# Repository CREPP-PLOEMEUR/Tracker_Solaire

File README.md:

<!--# Tracker solaire -->
<!--+ 2023-2024 -->
<!--$ C++-->
<!--$ Freecad -->
<!--$ GPS -->
<!--% Ce projet vise à concevoir et construire un système de suivi solaire spécialement conçu pour maximiser l'efficacité de la capture d'énergie solaire à partir d'un panneau solaire. -->
 -->
# Projet de Tracker Solaire pour Panneau 1m x 1m60

Ce projet vise à concevoir et construire un système de suivi solaire spécialement conçu pour maximiser l'efficacité de la capture d'énergie solaire à partir d'un panneau solaire de dimensions spécifiques.

## Table des matières

- [Aperçu](#aperçu)
- [Fonctionnalités](#fonctionnalités)
- [Matériaux](#matériaux)
- [Schémas et Conception](#schémas-et-conception)

## Aperçu

Ce projet a pour objectif de créer un tracker solaire qui ajuste automatiquement la position d'un panneau solaire de 1 mètre sur 1 mètre 60 pour suivre le mouvement du soleil tout au long de la journée. Cette optimisation permettra une captation maximale de l'énergie solaire disponible.

## Fonctionnalités

Le tracker solaire comprend différentes fonctionnalités :

- Suivi précis et automatique de la trajectoire du soleil pour maximiser la production d'énergie solaire.
- Utilisation d'un module GPS pour déterminer la position du panneau solaire.  Une fois la position captée, l'heure permet de calculer 
la position du Soleil à n'importe quel moment de la journée.
- Un module RTC (Real Time Clock) enregistre l'heure pour éviter de solliciter le module GPS
- Contrôle fluide des moteurs pour ajuster la position du panneau solaire 
- Interface de communication pour surveiller et configurer les performances du tracker.
- Tous les évènements sont enregistrés dans une carte microSD.
- Le tracker se met en veille profonde dès que la luminosité devient trop faible.
- Une rafale de vent, dont la consigne peut être ajustée par l'utilisateur, réveille en cas de besoin le tracker pour le mettre en position horizontale.

## Matériaux

- Composants électroniques standard tels que microcontrôleurs, GPS, moteurs pas à pas, etc.
- Carte de circuit imprimé spécialement conçue pour le tracker solaire.

- Moteurs pas à pas robustes adaptés aux dimensions du panneau solaire.
- Structure mécanique pour soutenir et orienter le panneau solaire.
- Source d'alimentation adaptée aux moteurs et à l'électronique.

## Schémas et Conception

Les schémas électriques détaillés et les plans de conception du circuit imprimé spécifique au tracker solaire sont disponibles dans le dossier `Hardware`.

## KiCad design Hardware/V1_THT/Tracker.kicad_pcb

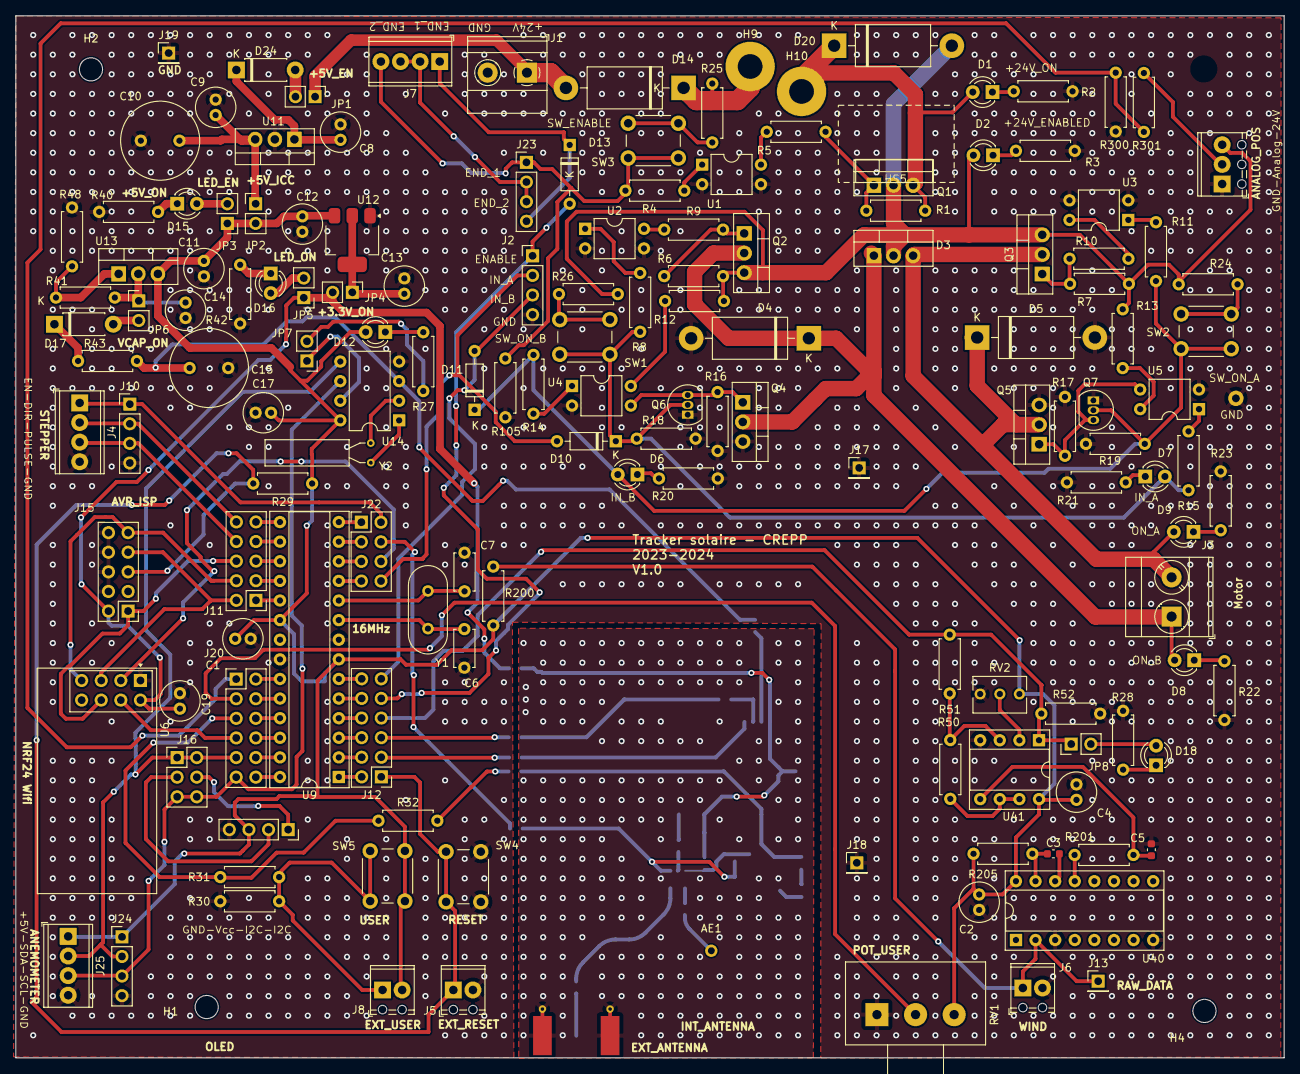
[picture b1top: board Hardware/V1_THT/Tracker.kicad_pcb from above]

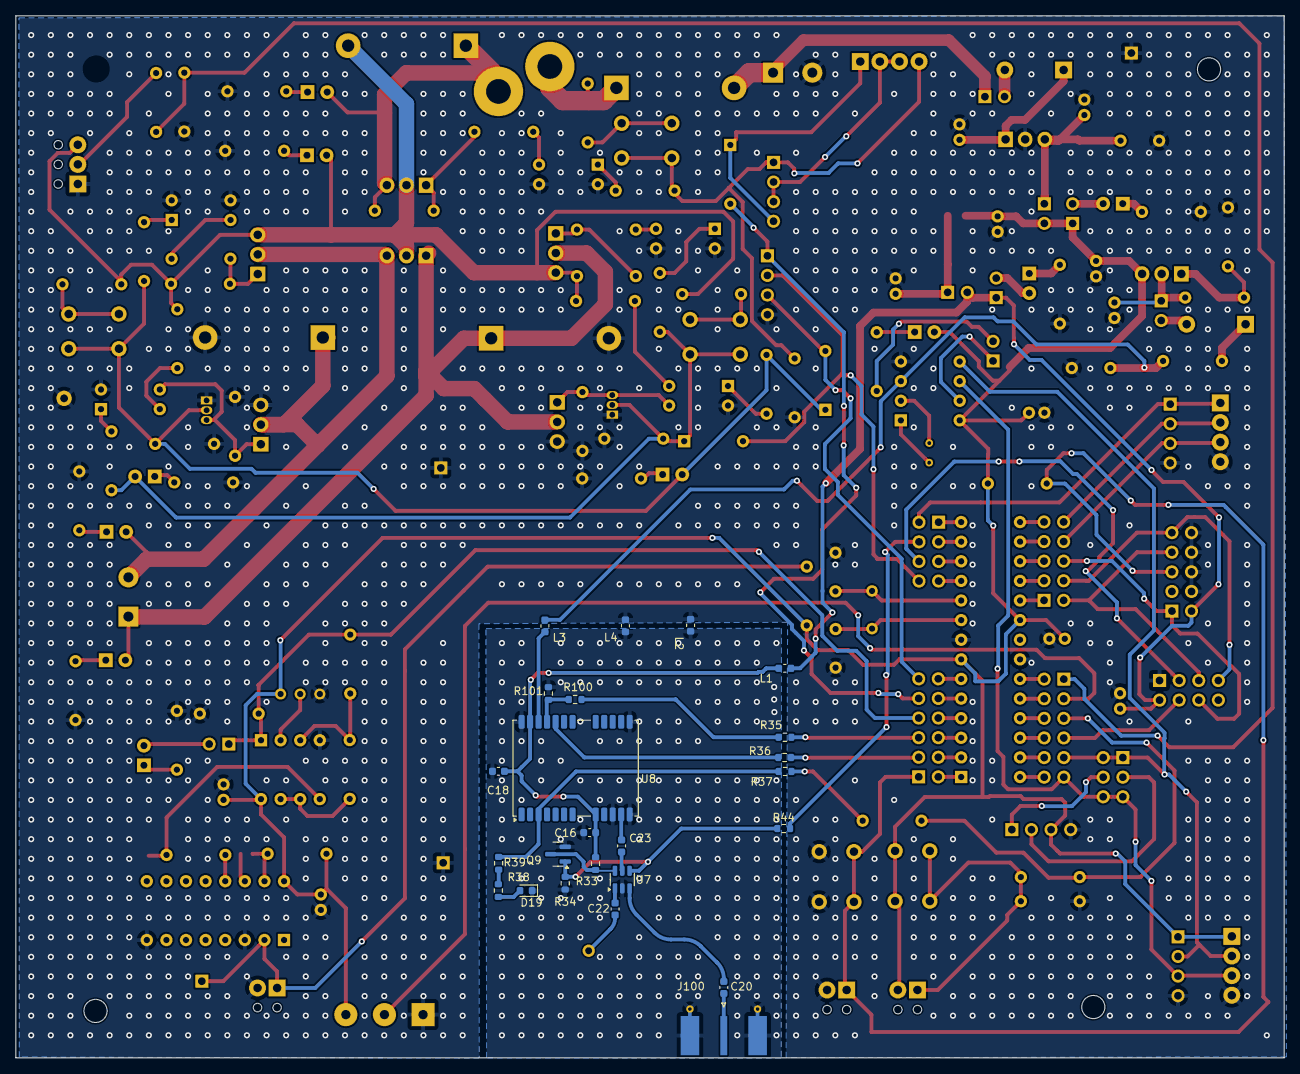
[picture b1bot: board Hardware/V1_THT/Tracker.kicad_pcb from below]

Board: 2 copper layers, 164.3 x 134.9 mm, 181 parts (24 on the bottom side), 132 nets.

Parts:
AE1: Internal_antenna; MountingHole_2.2mm_M2_DIN965_Pad
C1, C2, C4, C8, C9, C11, C12, C13, C14, C17, C19: 100nF; C_Radial_D5.0mm_H11.0mm_P2.00mm
C3, C5, C16, C18: 100nF; C_0603_1608Metric
C6, C7: 22pF; C_Disc_D4.7mm_W2.5mm_P5.00mm
C10: 1mF; C_Radial_D10.0mm_H16.0mm_P5.00mm
C15: 20F; C_Radial_D10.0mm_H20.0mm_P5.00mm
C20, C22, C23: 100pF; C_0603_1608Metric
D1, D2, D6, D7, D8, D9, D12, D15, D16, D18: LED; LED_D3.0mm
D3: D_Dual_CommonCathode_AAK; TO-220-3_Vertical
D4, D5, D14, D20: 1N5408; D_DO-201AD_P15.24mm_Horizontal
D10, D11, D13: 1N4148; D_DO-35_SOD27_P7.62mm_Horizontal
D17, D24: 1N4818; D_DO-41_SOD81_P7.62mm_Horizontal
D19: LED; LED_0603_1608Metric
H1, H2, H3, H4: MountingHole; MountingHole_3mm
H8: Probe_GND; Hole_1mm_Scope
H9, H10: MountingHole_Pad; MountingHole_3.2mm_M3_Pad
HS1, HS2, HS3, HS4, HS5: Heatsink; HeastSink_MOSFET_15mm_10mm_20mm
J1: +24V; TerminalBlock_Phoenix_MKDS-1,5-2-5.08_1x02_P5.08mm_Horizont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
J2, J10, J24: PinHeader_Control; PinHeader_1x04_P2.54mm_Vertical
J3: Motor; TerminalBlock_Phoenix_MKDS-3-2-5.08_1x02_P5.08mm_Horizontal
J4: Stepper; TerminalBlock_Phoenix_MPT-0,5-4-2.54_1x04_P2.54mm_Horizontal
J5, J8: USR_BTN; TerminalBlock_Phoenix_MPT-0,5-2-2.54_1x02_P2.54mm_Horizontal
J6: Wind; TerminalBlock_Phoenix_MPT-0,5-2-2.54_1x02_P2.54mm_Horizontal
J7: END_STOP_1_2; TerminalBlock_Phoenix_MPT-0,5-4-2.54_1x04_P2.54mm_Horizontal
J9: Analog_Position; TerminalBlock_Phoenix_MPT-0,5-3-2.54_1x03_P2.54mm_Horizontal
J11: Conn_02x05_Odd_Even; PinHeader_2x05_P2.54mm_Vertical
J12, J20: Conn_02x06_Odd_Even; PinHeader_2x06_P2.54mm_Vertical
J13: RAW_data_Wind; PinHeader_1x01_P2.54mm_Vertical
J14: OLED_SOCKET; PinSocket_1x04_P2.54mm_Vertical
J15: SPI_Programming; PinHeader_2x05_P2.54mm_Vertical
J16: I2C_Selector; PinHeader_2x03_P2.54mm_Vertical
J17, J18, J19: GND; PinHeader_1x01_P2.54mm_Vertical
J22: Conn_02x04_Odd_Even; PinHeader_2x04_P2.54mm_Vertical
J23: END_STOP_header; PinHeader_1x04_P2.54mm_Vertical
J25: Anemometer; TerminalBlock_Phoenix_MPT-0,5-4-2.54_1x04_P2.54mm_Horizontal
J100: 132134; SMA_Molex_73251-1153_EdgeMount_Horizontal
JP1, JP2, JP3, JP4, JP5, JP6, JP7, JP8: Jumper; PinHeader_1x02_P2.54mm_Vertical
L1, L2, L3, L4: L; L_0603_1608Metric
Q1, Q2, Q3: IRF4905; TO-220-3_Vertical
Q4, Q5: IRF520; TO-220-3_Vertical
Q6, Q7: 2N7000; TO-92_Inline
Q9: SI2302; SOT-23
R1, R25, R30, R31: 1k; R_Axial_DIN0207_L6.3mm_D2.5mm_P7.62mm_Horizontal
R2, R3, R22, R23: 3.3K; R_Axial_DIN0207_L6.3mm_D2.5mm_P7.62mm_Horizontal
R4, R8, R11, R14, R15: 120; R_Axial_DIN0207_L6.3mm_D2.5mm_P7.62mm_Horizontal
R5, R9, R10: 2.2K; R_Axial_DIN0207_L6.3mm_D2.5mm_P7.62mm_Horizontal
R6, R7, R12, R13: 1K; R_Axial_DIN0207_L6.3mm_D2.5mm_P7.62mm_Horizontal
R16, R17, R18, R19: 100k; R_Axial_DIN0207_L6.3mm_D2.5mm_P7.62mm_Horizontal
R20, R21, R27, R28, R40, R42: 270; R_Axial_DIN0207_L6.3mm_D2.5mm_P7.62mm_Horizontal
R24, R26: 2.7k; R_Axial_DIN0207_L6.3mm_D2.5mm_P7.62mm_Horizontal
R29, R50, R51, R52, R105, R201, R205, R300, R301: 10k; R_Axial_DIN0207_L6.3mm_D2.5mm_P7.62mm_Horizontal
R32: 2.2k; R_Axial_DIN0207_L6.3mm_D2.5mm_P7.62mm_Horizontal
R33, R100, R101: 1k; R_0603_1608Metric
R34: 10k; R_0603_1608Metric
R35, R36, R37, R39, R44: 0; R_0603_1608Metric
R38: 330; R_0603_1608Metric
R41, R43, R48: 100; R_Axial_DIN0207_L6.3mm_D2.5mm_P7.62mm_Horizontal
R200: 470k; R_Axial_DIN0207_L6.3mm_D2.5mm_P7.62mm_Horizontal
RV1: R_Potentiometer; Potentiometer_Alps_RK163_Single_Horizontal
RV2: R_Potentiometer; Potentiometer_Bourns_3266Y_Vertical
SW1: SW_A; SW_PUSH_6mm_H8mm
SW2, SW4: SW_B; SW_PUSH_6mm_H8mm
SW3: SW_E; SW_PUSH_6mm_H8mm
SW5: SW_User; SW_PUSH_6mm_H8mm
U1, U2, U3, U4, U5: PC817; DIP-4_W7.62mm
U6: NRF24L01_Breakout; nRF24L01_Breakout
U7: AS193-73; SOT-23-6
U8: NEO-M8M; ublox_NEO
U9: ATmega328P-P; DIP-28_W7.62mm_Socket
U11: L7805; TO-220-3_Vertical
U12: AMS1117-3.3; SOT-223-3_TabPin2
U13: LM317_TO-220; TO-220-3_Vertical
U14: DS1307+; DIP-8_W7.62mm
U40: 74HC123; DIP-16_W7.62mm_Socket
U41: LM358; DIP-8_W7.62mm_Socket
Y1: 16MHz; Crystal_HC49-4H_Vertical
Y2: 16MHz; Crystal_AT310_D3.0mm_L10.0mm_Horizontal

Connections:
+3.3V: C19.1, J15.2, JP4.2 (B), JP5.1 (A), L1.1, U6.2 (VCC)
+3.3V_GNSS: C16.2, C18.2, L1.2, R33.2, U8.8 (~RESET), U8.23 (VCC)
+5V: C1.2, C2.1, C4.1, C11.1, C12.1, C17.2, D12.2 (A), J8.2, J14.3, J24.1, J25.1, JP2.2 (B), JP3.1 (A), R29.1, R200.1, R205.1, RV1.3, RV2.1, SW5.1 (A), U9.7 (VCC), U9.20 (AVCC), U12.3 (VI), U13.3 (VI), U14.8 (VCC), U40.16 (VCC), U41.8 (V+)
+24V: D14.2 (A), J1.1, JP1.1 (A)
+VCC_Motor: D2.2 (A), D3.2 (K), D20.2 (A), J9.3, Q1.2 (D), Q2.3 (S), Q3.3 (S), R6.1, R7.1, R12.1, R13.1, R24.1, R26.1
+VCap: C15.1, L3.1, R43.2, U14.3 (VBAT)
+VCap_GNSS: L3.2, U8.22 (V_BCKP)
/Anemometer/SCL: J16.5, J16.6, J20.11, J24.3, J25.3, U14.6 (SCL)
/Anemometer/SDA: J16.1, J16.2, J20.9, J24.2, J25.2, U14.5 (SDA)
/Crystal/XTAl_1: C6.2, U9.9 (XTAL1/PB6), Y1.2
/Crystal/XTAl_2: C7.2, U9.10 (XTAL2/PB7), Y1.1
/GNSS/RX: J12.3, R36.1
/GNSS/TX: J12.5, R35.1
/GNSS/~INTERNAL_ANTENNA: Q9.1 (G), R34.2, R44.1, U7.4 (V2)
/MCU/CLK: J11.2, J15.7, U6.5 (SCK)
/MCU/MISO: J11.4, J15.9, U6.7 (MISO)
/MCU/MOSI: J11.6, J15.1, U6.6 (MOSI)
/MCU/PB0: J22.1, U9.14 (PB0)
/MCU/PB0-D8: J4.1, J10.1, J22.2
/MCU/PB1-D9~: J4.2, J10.2, J11.10
/MCU/PB2-D10~: J4.3, J10.3, J11.8
/MCU/PC0-A0: J20.1, R300.2, R301.2
/MCU/PC1-A1: J20.3, RV1.2
/MCU/PC3-A3: J20.7, U6.4 (~CSN)
/MCU/PD2-D2-(INT0): J12.7, JP8.1 (A), R51.2, R52.2, U41.1
/MCU/PD3-D3-(INT1)~: D13.2 (A), J2.1, J12.9
/MCU/PD4-D4: D11.2 (A), J2.3, J12.11
/MCU/PD5-D5~: D10.2 (A), J2.2, J22.8
/MCU/PD6-D6~: J22.6, U6.3 (CE)
/MCU/PD7-D7: J22.4, R44.2
/Motors/ENABLE: D13.1 (K), J7.1, J23.4
/Motors/IN_A: D7.2 (A), D10.1 (K), Q6.2 (G), R8.1, R15.2, R18.1, SW1.1 (A)
/Motors/IN_B: D6.2 (A), D11.1 (K), Q7.2 (G), R11.2, R14.1, R19.1, SW2.1 (A)
/OLED/A: J14.1, J16.4
/OLED/B: J14.2, J16.3
/Power_Supply/Vcapa: C14.1, JP6.1 (A), R41.2, U13.2 (VO)
/RST: J5.1, J12.1, J15.5, R29.2, SW4.2 (B)
/TIMEPULSE: R32.2, R37.2
/UserActions/Button: J8.1, R30.1, R31.2, SW5.2 (B)
/V_{A_{2}}: J20.5, R31.1, R32.1
GND: C1.1, C2.2, C4.2, C5.2, C6.1, C7.1, C8.2, C9.2, C10.2, C11.2, C12.2, C13.2, C14.2, C15.2, C17.1, C19.2, D4.2 (A), D5.2 (A), H8.1, J1.2, J2.4, J4.4, J5.2, J6.2, J9.1, J10.4, J14.4, J15.4, J15.6, J15.8, J15.10, J17.1, J18.1, J19.1, J24.4, J25.4, L2.1, L4.1, Q4.3 (S), Q5.3 (S), Q6.1 (S), Q7.1 (S), R2.2, R3.2, R16.2, R17.2, R18.2, R19.2, R20.2, R21.2, R22.2, R23.2, R28.2, R30.2, R40.2, R42.2, R48.1, R52.1, R105.2, R300.1, RV1.1, RV2.3, SW4.1 (A), U1.2, U1.3, U2.2, U2.3, U3.2, U3.3, U4.2, U5.2, U6.1 (GND), U9.8 (GND), U9.22 (GND), U11.2 (GND), U12.1 (GND), U14.4 (GND), U40.3 (Clr), U40.8 (GND), U41.4 (V-)
GND_GNSS: C16.1, C18.1, D19.1 (K), J100.2 (Ext), L2.2, L4.2, Q9.2 (S), R34.1, R101.2, U7.2 (GND), U8.10 (GND), U8.12 (GND), U8.13 (GND), U8.24 (GND)
unnamed: AE1.1 (A), C22.1
unnamed: D1.2 (A), D20.1 (K), H10.1, Q1.3 (S), R1.2
unnamed: D1.1 (K), R2.1
unnamed: D2.1 (K), R3.1
unnamed: D3.1 (A), D4.1 (K), D8.2 (A), J3.1, Q2.2 (D), Q4.2 (D)
unnamed: D3.3 (A), D5.1 (K), D9.2 (A), J3.2, Q3.2 (D), Q5.2 (D)
unnamed: D6.1 (K), R20.1
unnamed: D7.1 (K), R21.1
unnamed: D8.1 (K), R22.1
unnamed: D9.1 (K), R23.1
unnamed: D12.1 (K), R27.1
unnamed: D14.1 (K), H9.1, R25.1
unnamed: D15.2 (A), JP3.2 (B)
unnamed: D15.1 (K), R40.1
unnamed: D16.2 (A), JP5.2 (B)
unnamed: D16.1 (K), R42.1
unnamed: D17.2 (A), JP6.2 (B)
unnamed: D17.1 (K), R43.1
unnamed: D18.2 (A), JP8.2 (B)
unnamed: D18.1 (K), R28.1
unnamed: D19.2 (A), R38.1
unnamed: D24.2 (A), JP1.2 (B)
unnamed: C8.1, D24.1 (K), U11.1 (IN)
unnamed: J9.2, R301.1
unnamed: J11.1, U9.19 (PB5)
unnamed: J11.3, U9.18 (PB4)
unnamed: J11.5, U9.17 (PB3)
unnamed: J11.7, U9.16 (PB2)
unnamed: J11.9, U9.15 (PB1)
unnamed: J12.2, U9.1 (~RESET/PC6)
unnamed: J12.4, U9.2 (PD0)
unnamed: J12.6, U9.3 (PD1)
unnamed: J12.8, U9.4 (PD2)
unnamed: J12.10, U9.5 (PD3)
unnamed: J12.12, U9.6 (PD4)
unnamed: J6.1, J13.1, R200.2, U40.2 (B)
unnamed: J20.2, U9.23 (PC0)
unnamed: J20.4, U9.24 (PC1)
unnamed: J20.6, U9.25 (PC2)
unnamed: J20.8, U9.26 (PC3)
unnamed: J20.10, U9.27 (PC4)
unnamed: J20.12, U9.28 (PC5)
unnamed: J22.3, U9.13 (PD7)
unnamed: J22.5, U9.12 (PD6)
unnamed: J22.7, U9.11 (PD5)
unnamed: J7.4, J23.1, R4.1, R105.1, SW3.1 (A)
unnamed: J7.2, J7.3, J23.2, J23.3
unnamed: C20.1, J100.1 (In)
unnamed: C9.1, C10.1, JP2.1 (A), U11.3 (OUT)
unnamed: C13.1, JP4.1 (A), U12.2 (VO)
unnamed: JP7.1 (A), U14.7 (SQW/OUT)
unnamed: JP7.2 (B), R27.2
unnamed: Q1.1 (G), R1.1, R5.2
unnamed: Q2.1 (G), R6.2, R9.2
unnamed: Q3.1 (G), R7.2, R10.2
unnamed: Q4.1 (G), Q6.3 (D), R16.1, U4.3
unnamed: Q5.1 (G), Q7.3 (D), R17.1, U5.3
unnamed: Q9.3 (D), R33.1, U7.6 (V1)
unnamed: R4.2, U1.1
unnamed: R5.1, U1.4
unnamed: R8.2, U2.1
unnamed: R9.1, U2.4
unnamed: R10.1, U3.4
unnamed: R11.1, U3.1
unnamed: R12.2, U4.4
unnamed: R13.2, U5.4
unnamed: R14.2, U4.1
unnamed: R15.1, U5.1
unnamed: R38.2, R39.1
unnamed: R35.2, R100.1
unnamed: R26.2, SW1.2 (B)
unnamed: R24.2, SW2.2 (B)
unnamed: R25.2, SW3.2 (B)
unnamed: C22.2, U7.1 (RF1)
unnamed: C20.2, U7.3 (RF2)
unnamed: C23.1, U7.5 (RFC)
unnamed: C23.2, U8.11 (RF_IN)
unnamed: R100.2, R101.1, U8.21 (RXD/SPI_MOSI)
unnamed: R37.1, R39.2, U8.3 (TIMEPULSE)
unnamed: R36.2, U8.20 (TXD/SPI_MISO)
unnamed: R41.1, R48.2, U13.1 (ADJ)
unnamed: U14.1 (X1), Y2.2
unnamed: U14.2 (X2), Y2.1
unnamed: C3.2, U40.14 (Cext)
unnamed: R201.1, U40.13 (Q)
unnamed: C3.1, R205.2, U40.15 (RCext)
unnamed: R50.2, R51.1, U41.3 (+)
unnamed: RV2.2, U41.2 (-)
unnamed: C5.1, R201.2, U41.5 (+)
unnamed: R50.1, U41.6 (-), U41.7

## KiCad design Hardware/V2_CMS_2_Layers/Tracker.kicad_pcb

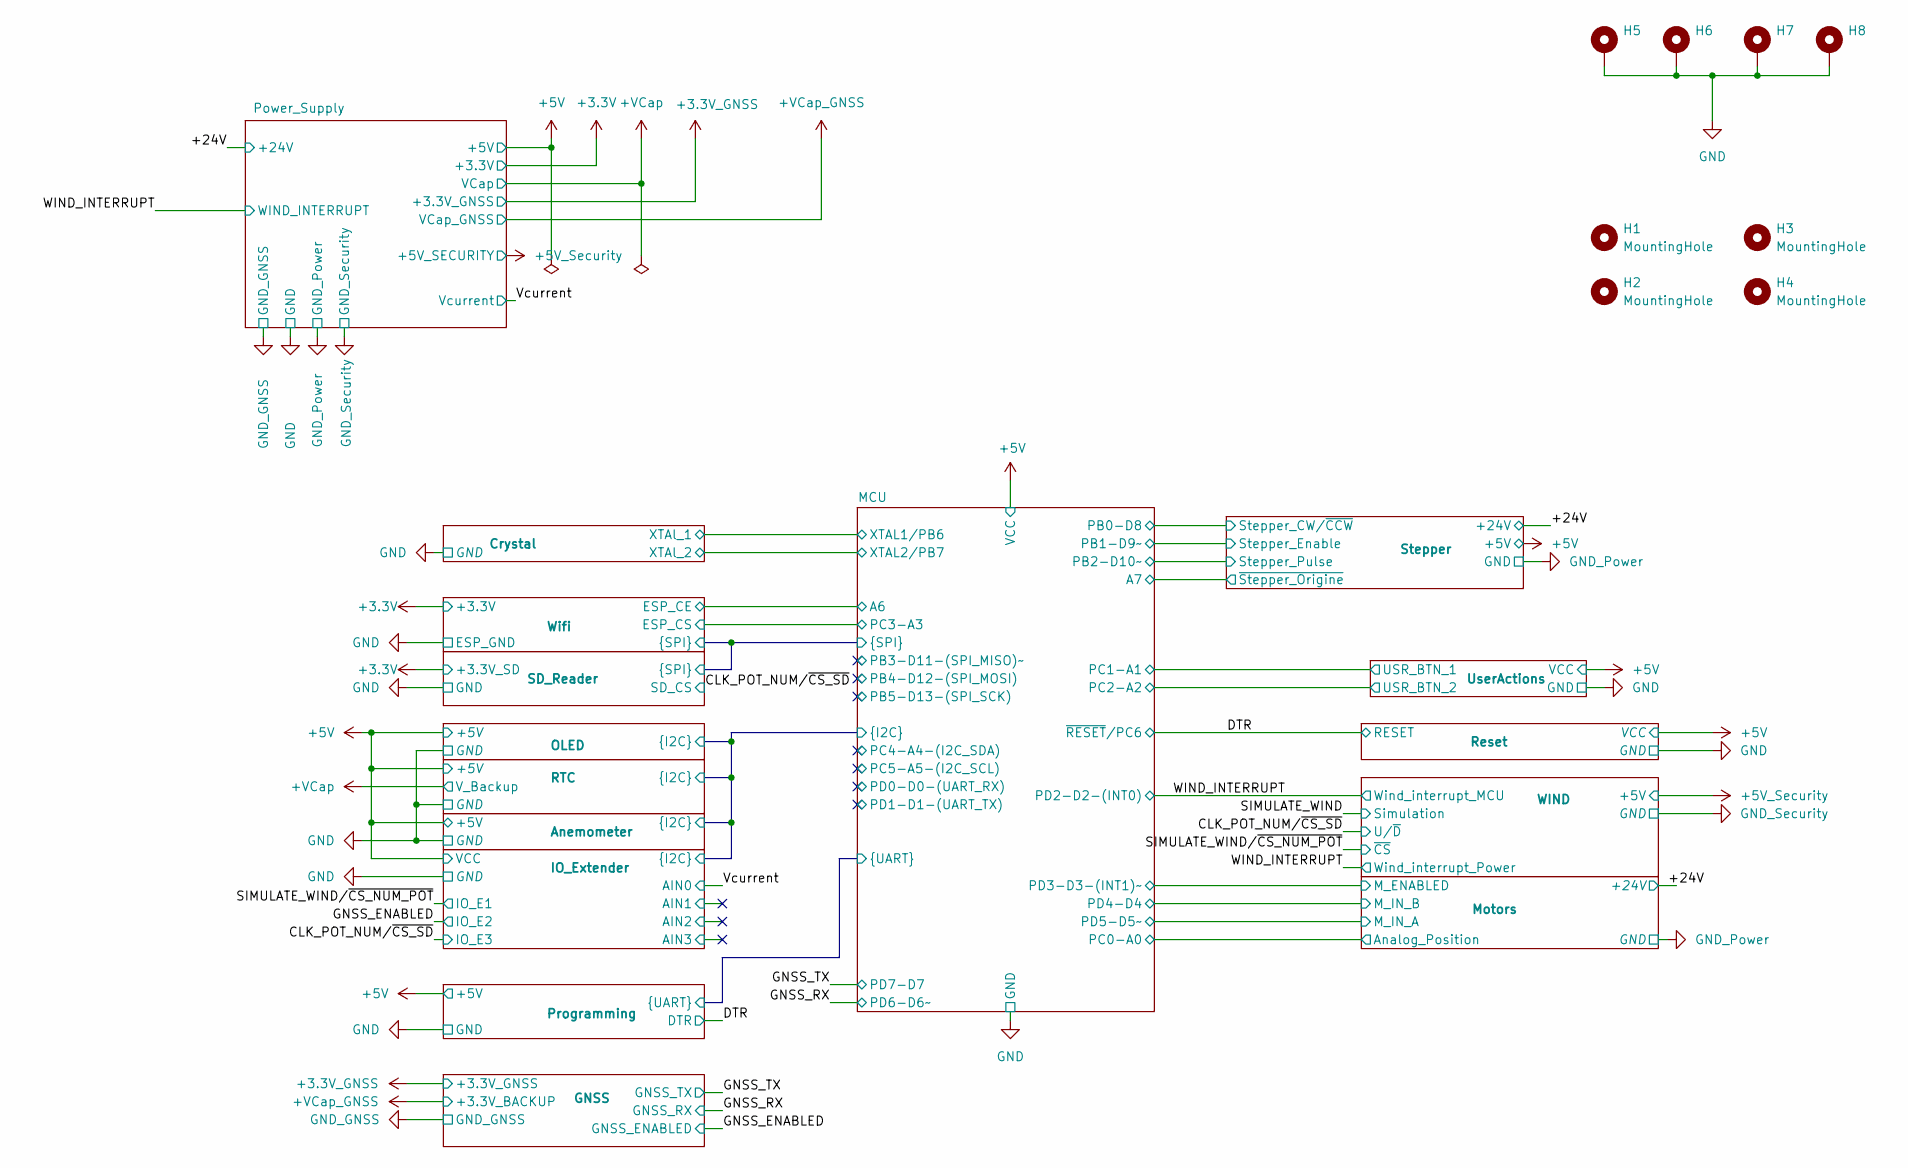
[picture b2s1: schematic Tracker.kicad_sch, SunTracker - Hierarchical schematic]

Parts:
H1, H2, H3, H4: MountingHole; MountingHole_3mm
H5, H6, H7, H8: Probe_GND; Hole_1mm_Scope

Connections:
unnamed: H5.1, H6.1, H7.1, H8.1

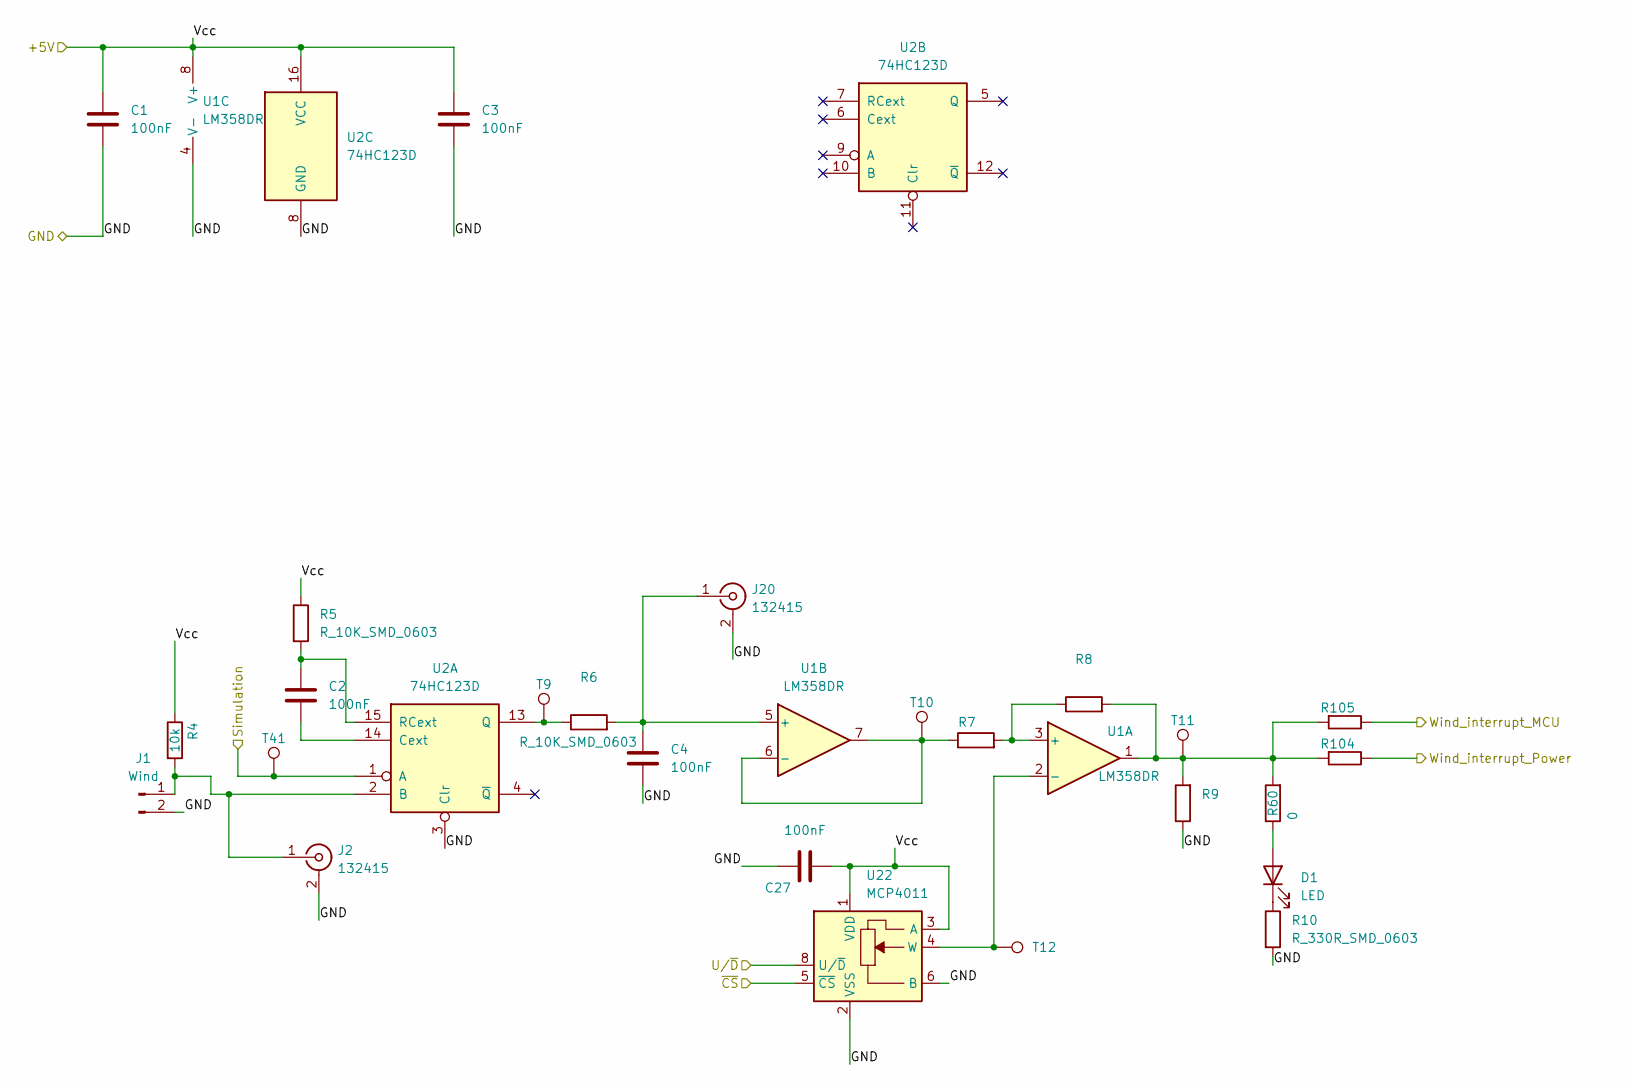
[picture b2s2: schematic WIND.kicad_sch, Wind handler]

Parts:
C1, C2, C3, C4, C27: 100nF; C_0603_1608Metric
D1: LED; LED_0603_1608Metric
J1: Wind; TerminalBlock_Phoenix_MPT-0,5-2-2.54_1x02_P2.54mm_Horizontal
J2, J20: 132415; SMA_Molex_73251-1153_EdgeMount_Horizontal
R4: 10k; R_0603_1608Metric
R5, R6, R7, R8, R9: R_10K_SMD_0603; R_0603_1608Metric
R10: R_330R_SMD_0603; R_0603_1608Metric
R60: 0; R_0603_1608Metric
R104, R105: R_0R_SMD_0603; R_0603_1608Metric
T9, T10, T11, T12, T41: TP; TestPoint_Pad_D1.0mm
U1: LM358DR; TSSOP-8_4.4x3mm_P0.65mm
U2: 74HC123D; SOIC-16W_5.3x10.2mm_P1.27mm
U22: MCP4011; SOIC-8_3.9x4.9mm_P1.27mm

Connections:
/CLK_POT_NUM/~CS_SD: U22.8 (U/~D); also elsewhere on the board
/SIMULATE_WIND: T41.1, U2.1 (A)
/SIMULATE_WIND/~CS_NUM_POT: U22.5 (~CS); also elsewhere on the board
/WIND_INTERRUPT: R104.2, R105.2; also elsewhere on the board
unnamed: D1.2 (A), R60.1
unnamed: D1.1 (K), R10.1
unnamed: J1.1, J2.1 (In), R4.2, U2.2 (B)
unnamed: C4.1, J20.1 (In), R6.2, U1.5 (+)
unnamed: R8.2, R9.2, R60.2, R104.1, R105.1, T11.1, U1.1
unnamed: R7.2, R8.1, U1.3 (+)
unnamed: T12.1, U1.2 (-), U22.4 (W)
unnamed: R7.1, T10.1, U1.6 (-), U1.7
unnamed: C2.2, U2.14 (Cext)
unnamed: R6.1, T9.1, U2.13 (Q)
unnamed: C2.1, R5.2, U2.15 (RCext)

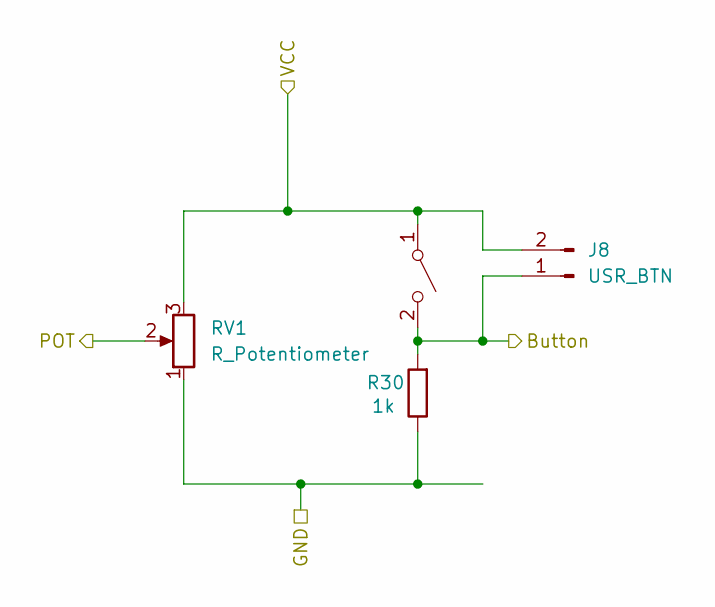
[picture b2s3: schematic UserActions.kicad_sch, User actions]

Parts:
J8: USR_BTN; TerminalBlock_Phoenix_MPT-0,5-2-2.54_1x02_P2.54mm_Horizontal
R30: 1k; R_Axial_DIN0207_L6.3mm_D2.5mm_P7.62mm_Horizontal
RV1: R_Potentiometer; Potentiometer_Alps_RK163_Single_Horizontal
SW5: SW_User; SW_PUSH_6mm_H8mm

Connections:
unnamed 225: RV1.2; also elsewhere on the board

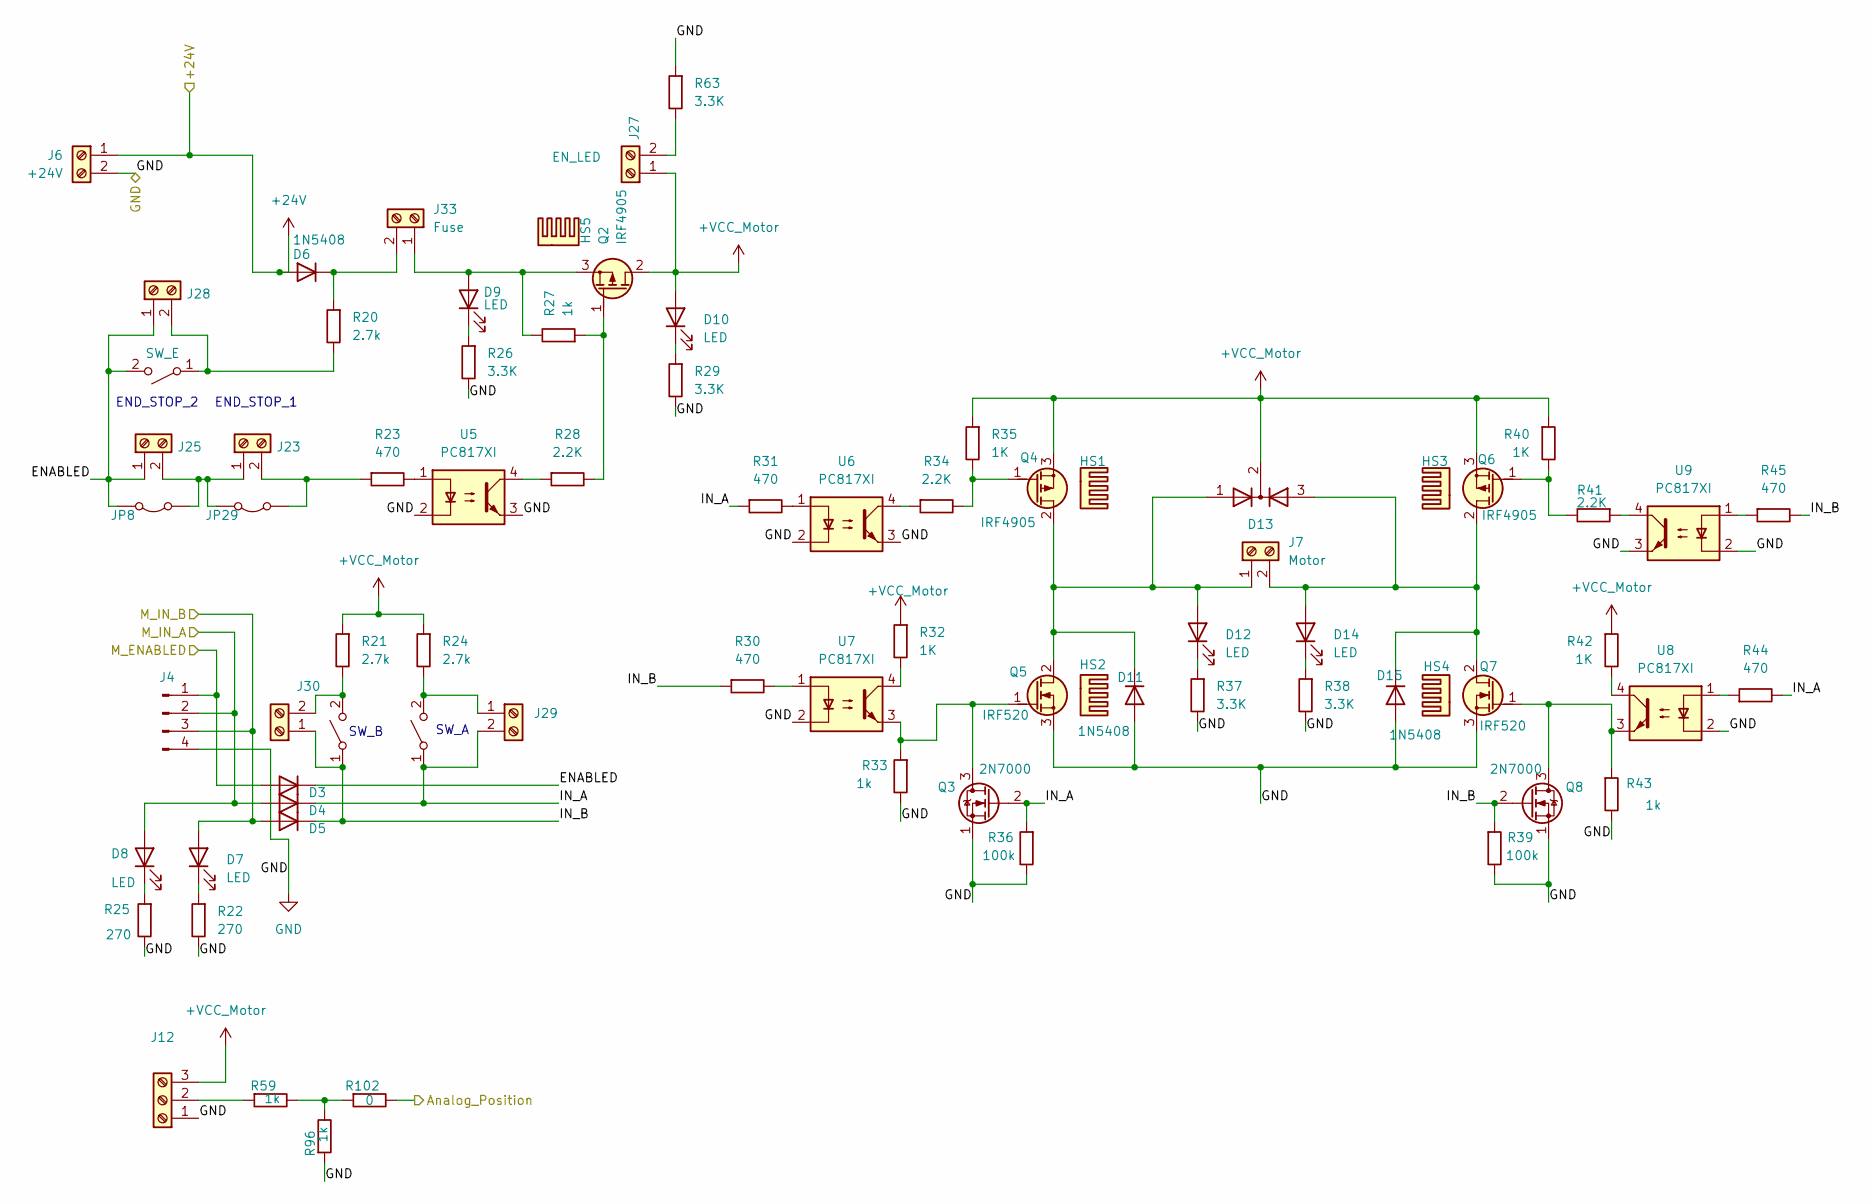
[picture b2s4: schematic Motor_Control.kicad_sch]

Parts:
D3, D4, D5: 1N4148; D_SOD-323
D6, D11, D15: 1N5408; D_DO-201AD_P15.24mm_Horizontal
D7, D8, D9, D10, D12, D14: LED; LED_0603_1608Metric
D13: D_Dual_CommonCathode_AAK; TO-220-3_Vertical
HS1, HS2, HS3, HS4, HS5: Heatsink; HeastSink_MOSFET_15mm_10mm_20mm
J4: PinHeader_Control; PinHeader_1x04_P2.54mm_Vertical
J6: +24V; PhoenixContact_MSTBA_2,5_2-G-5,08_1x02_P5.08mm_Horizontal
J7: Motor; PhoenixContact_MSTBA_2,5_2-G-5,08_1x02_P5.08mm_Horizontal
J12: KF128-2.54_3P; TerminalBlock_Phoenix_MPT-0,5-3-2.54_1x03_P2.54mm_Horizontal
J23, J25, J28, J29, J30: KF128-2.54_2P; TerminalBlock_Phoenix_MPT-0,5-2-2.54_1x02_P2.54mm_Horizontal
J27: EN_LED; TerminalBlock_Phoenix_MPT-0,5-2-2.54_1x02_P2.54mm_Horizontal
J33: Fuse; PhoenixContact_MSTBA_2,5_2-G-5,08_1x02_P5.08mm_Horizontal
JP8, JP29: Jumper; PinHeader_1x02_P2.54mm_Vertical
Q2, Q4, Q6: IRF4905; TO-220-3_Vertical
Q3, Q8: 2N7000; SOT-23-3
Q5, Q7: IRF520; TO-220-3_Vertical
R20, R21, R24: 2.7k; R_0603_1608Metric
R22, R25: 270; R_0603_1608Metric
R23, R30, R31, R44, R45: 470; R_0603_1608Metric
R26, R29, R37, R38, R63: 3.3K; R_0603_1608Metric
R27, R33, R43, R59, R96: 1k; R_0603_1608Metric
R28, R34, R41: 2.2K; R_0603_1608Metric
R32, R35, R40, R42: 1K; R_0603_1608Metric
R36, R39: 100k; R_0603_1608Metric
R102: 0; R_0603_1608Metric
SW1: SW_E; SW_Push_1P1T_NO_CK_KSC7xxJ
SW2, SW3: PB_SMD_12V_50MA_6MM_6MM; SW_Push_1P1T_NO_CK_KSC7xxJ
U5, U6, U7, U8, U9: PC817XI; SOP-4_4.4x2.6mm_P1.27mm

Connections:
+24V: D6.2 (A), J6.1; also elsewhere on the board
+VCC_Motor: D10.2 (A), D13.2 (K), J12.3, J27.1, Q2.2 (D), Q4.3 (S), Q6.3 (S), R21.1, R24.1, R32.1, R35.1, R40.1, R42.1
/MCU/PC0-A0: R102.2; also elsewhere on the board
/MCU/PD3-D3-(INT1)~: D3.2 (A), J4.1; also elsewhere on the board
/MCU/PD4-D4: D5.2 (A), D7.2 (A), J4.3; also elsewhere on the board
/MCU/PD5-D5~: D4.2 (A), D8.2 (A), J4.2; also elsewhere on the board
/Motors/ENABLED: D3.1 (K), J25.1, J28.1, JP8.2 (B), SW1.2 (B)
/Motors/IN_A: D4.1 (K), J29.2, Q3.2 (G), R31.1, R36.1, R44.2, SW3.1 (A)
unnamed: D6.1 (K), J33.2, R20.1
unnamed: D7.1 (K), R22.1
unnamed: D8.1 (K), R25.1
unnamed: D9.2 (A), J33.1, Q2.3 (S), R27.2
unnamed: D9.1 (K), R26.1
unnamed: D10.1 (K), R29.1
unnamed: D11.1 (K), D12.2 (A), D13.1 (A), J7.1, Q4.2 (D), Q5.2 (D)
unnamed: D12.1 (K), R37.1
unnamed: D13.3 (A), D14.2 (A), D15.1 (K), J7.2, Q6.2 (D), Q7.2 (D)
unnamed: D14.1 (K), R38.1
unnamed: J12.2, R59.1
unnamed: J23.1, J25.2, JP8.1 (A), JP29.2 (B)
unnamed: J23.2, JP29.1 (A), R23.1
unnamed: J27.2, R63.2
unnamed: J28.2, R20.2, SW1.1 (A)
unnamed: J29.1, R24.2, SW3.2 (B)
unnamed: J30.2, R21.2, SW2.2 (B)
unnamed: Q2.1 (G), R27.1, R28.2
unnamed: Q3.3 (D), Q5.1 (G), R33.1, U7.3
unnamed: Q4.1 (G), R34.2, R35.2
unnamed: Q6.1 (G), R40.2, R41.2
unnamed: Q7.1 (G), Q8.3 (D), R43.1, U8.3
unnamed: R23.2, U5.1
unnamed: R28.1, U5.4
unnamed: R31.2, U6.1
unnamed: R32.2, U7.4
unnamed: R34.1, U6.4
unnamed: R41.1, U9.4
unnamed: R42.2, U8.4
unnamed: R44.1, U8.1
unnamed: R45.1, U9.1
unnamed: R59.2, R96.2, R102.1

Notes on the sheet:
END_STOP_1
END_STOP_2
SW_B
SW_A

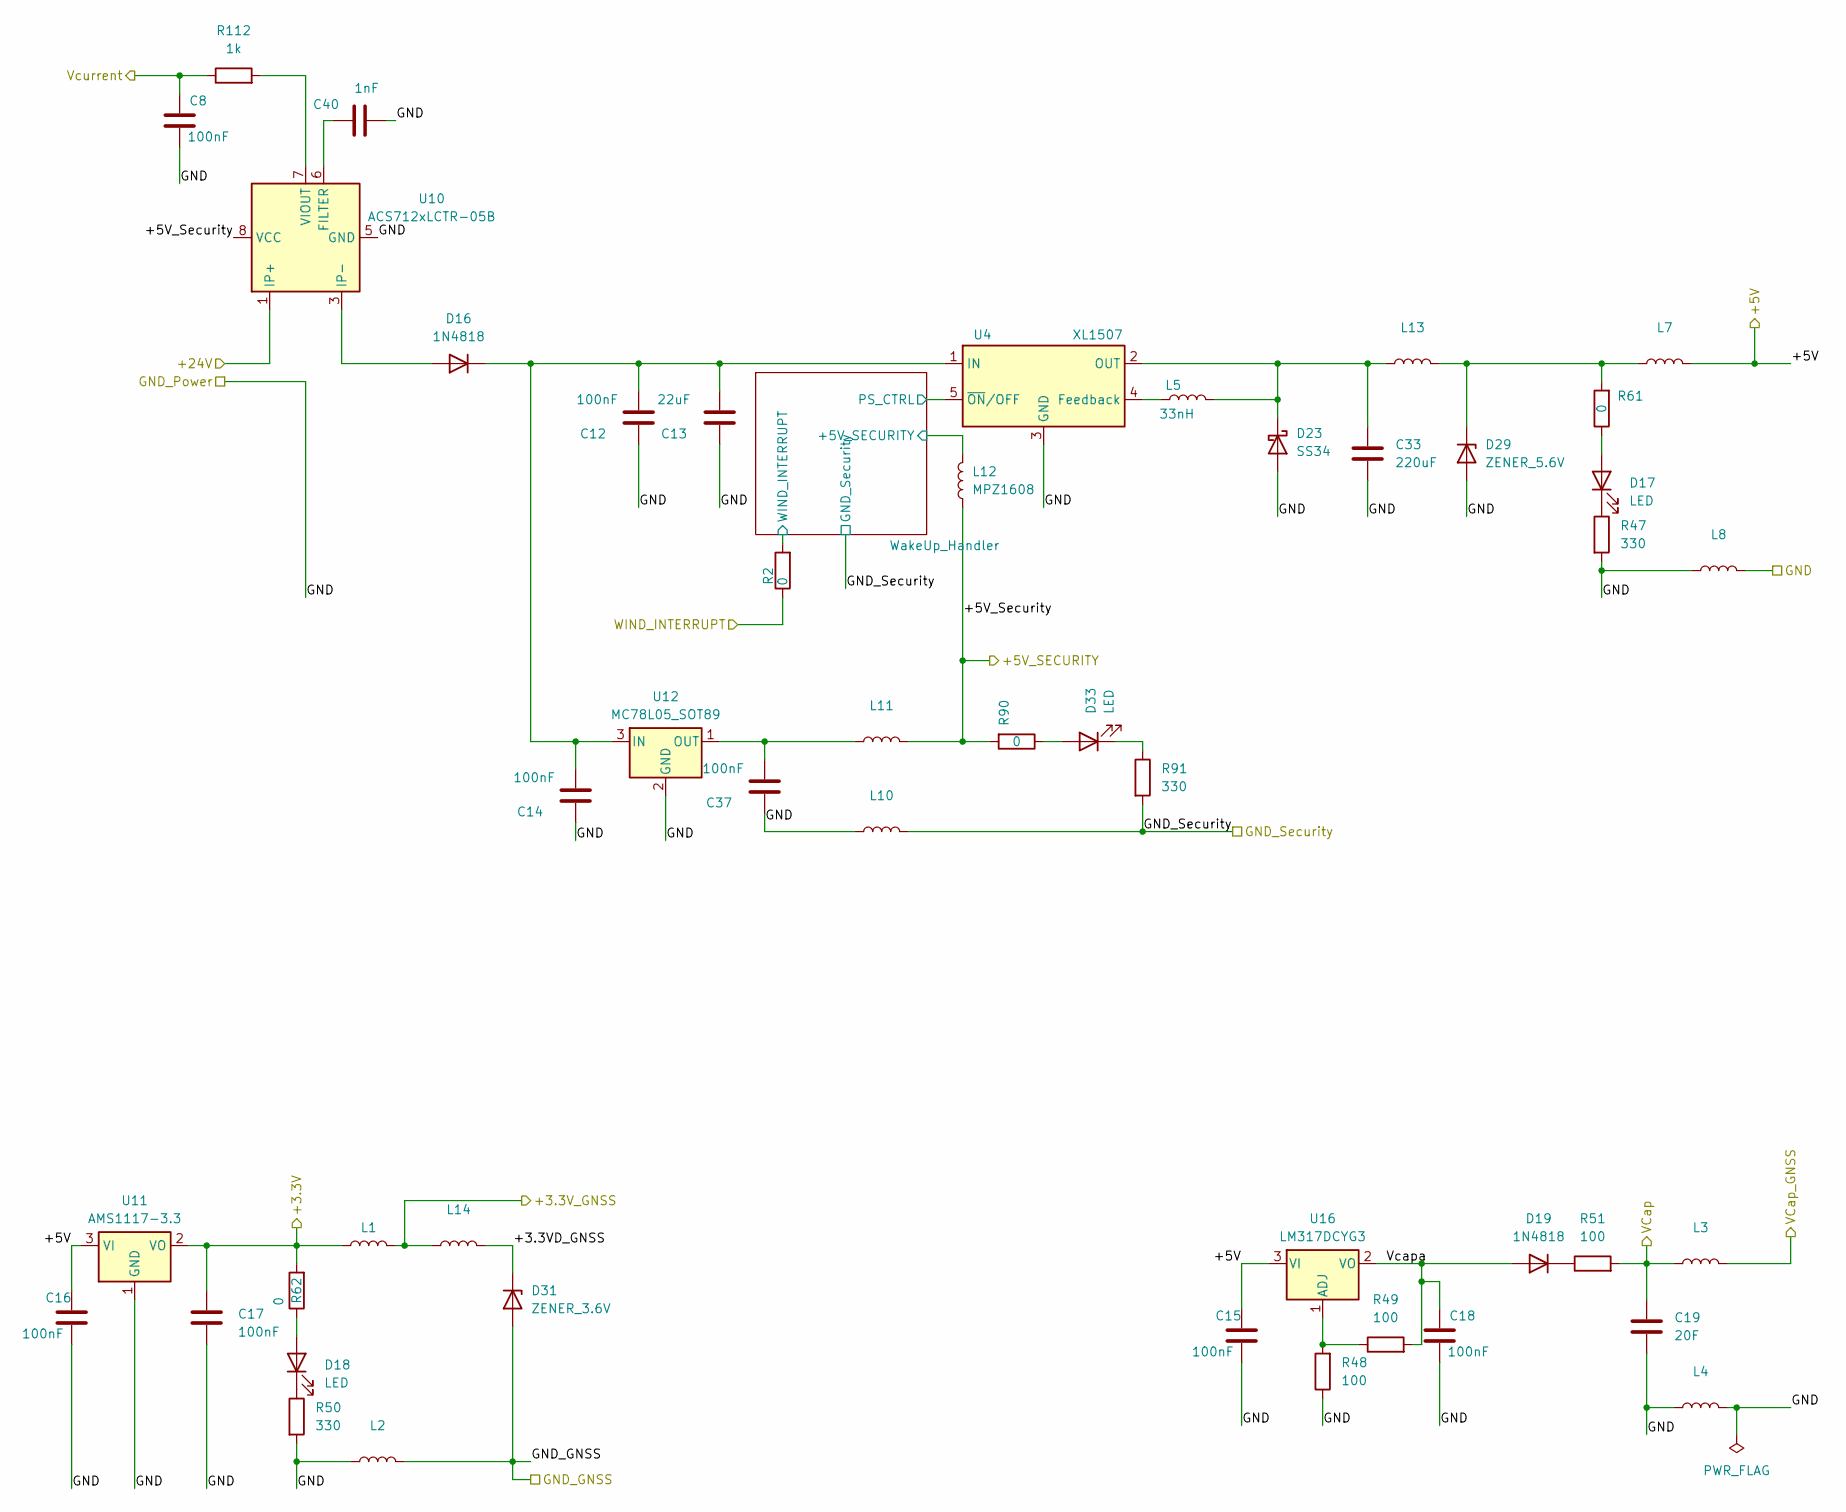
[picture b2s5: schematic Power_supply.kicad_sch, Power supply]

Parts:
C8, C12, C14, C15, C16, C17, C18, C37: 100nF; C_0603_1608Metric
C13: 22uF; C_0603_1608Metric
C19: 20F; C_Radial_D10.0mm_H20.0mm_P5.00mm
C33: 220uF; CP_Elec_6.3x7.7
C40: 1nF; C_0603_1608Metric
D16, D19: 1N4818; D_SOD-323
D17, D18, D33: LED; LED_0603_1608Metric
D23: SS34; D_SMA
D29: ZENER_5.6V; D_MiniMELF
D31: ZENER_3.6V; D_MiniMELF
L1, L2, L3, L4, L7, L8, L10, L11, L13, L14: MPZ1608S101ATAH0; L_0603_1608Metric
L5: 33nH; L_Wuerth_HCI-5040
L12: MPZ1608; L_0603_1608Metric
R2, R61, R62, R90: 0; R_0603_1608Metric
R47, R50, R91: 330; R_0603_1608Metric
R48, R49, R51: 100; R_0603_1608Metric
R112: 1k; R_0603_1608Metric
U4: XL1507; TO-252-5_TabPin3
U10: ACS712xLCTR-05B; SOIC-8_3.9x4.9mm_P1.27mm
U11: AMS1117-3.3; SOT-223-3_TabPin2
U12: MC78L05_SOT89; SOT-89-3
U16: LM317DCYG3; SOT-223-3_TabPin2

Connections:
+3.3V: C17.1, L1.1, R62.2, U11.2 (VO); also elsewhere on the board
+24V: U10.1 (IP+), U10.2 (IP+); also elsewhere on the board
+VCap: C19.1, L3.1, R51.2; also elsewhere on the board
+VCap_GNSS: L3.2; also elsewhere on the board
/Power_Supply/+3.3VD_GNSS: D31.1 (K), L14.2
/Power_Supply/Vcapa: C18.1, D19.2 (A), R49.2, U16.2 (VO)
/Power_Supply/WakeUp_Handler/PS_CTRL: U4.5 (~ON/OFF); also elsewhere on the board
/Power_Supply/WakeUp_Handler/WIND_INTERRUPT: R2.2; also elsewhere on the board
/WIND_INTERRUPT: R2.1; also elsewhere on the board
unnamed: D16.2 (A), U10.3 (IP-), U10.4 (IP-)
unnamed: C12.1, C13.1, C14.1, D16.1 (K), U4.1 (IN), U12.3 (IN)
unnamed: D17.2 (A), R61.1
unnamed: D17.1 (K), R47.1
unnamed: D18.2 (A), R62.1
unnamed: D18.1 (K), R50.1
unnamed: D19.1 (K), R51.1
unnamed: C33.1, D23.1 (K), L5.2, L13.1, U4.2 (OUT)
unnamed: D29.1 (K), L7.1, L13.2, R61.2
unnamed: D33.2 (A), R90.1
unnamed: D33.1 (K), R91.1
unnamed: L5.1, U4.4 (Feedback)
unnamed: C40.1, U10.6 (FILTER)
unnamed: R112.2, U10.7 (VIOUT)
unnamed: C37.1, L11.1, U12.1 (OUT)
unnamed: R48.2, R49.1, U16.1 (ADJ)
